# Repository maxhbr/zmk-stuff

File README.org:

#+title: Readme

* Building a Redox Style Split with xiaos + Shift Registers

similar to https://github.com/maxhbr/redox-meets-dao-choc-ble, but with a different set of electronics.

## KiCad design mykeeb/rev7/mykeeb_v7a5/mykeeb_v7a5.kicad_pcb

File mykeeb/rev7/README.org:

#+title: Readme

* Building a Redox Style Split with xiaos + Shift Registers

similar to https://github.com/maxhbr/redox-meets-dao-choc-ble, but with a different set of electronics.

*The shift registers are dropped for now, to iterate faster*

** The Idea:
*** Take the electronics from revxlp / uninarf
- Maybe with potential for (partial) JLC PCBA assembly
- using the xiao footprint from the TOTEM
*** Take the Rough layout from Redox
*** Adopt to the pinky stagger from the Kyria

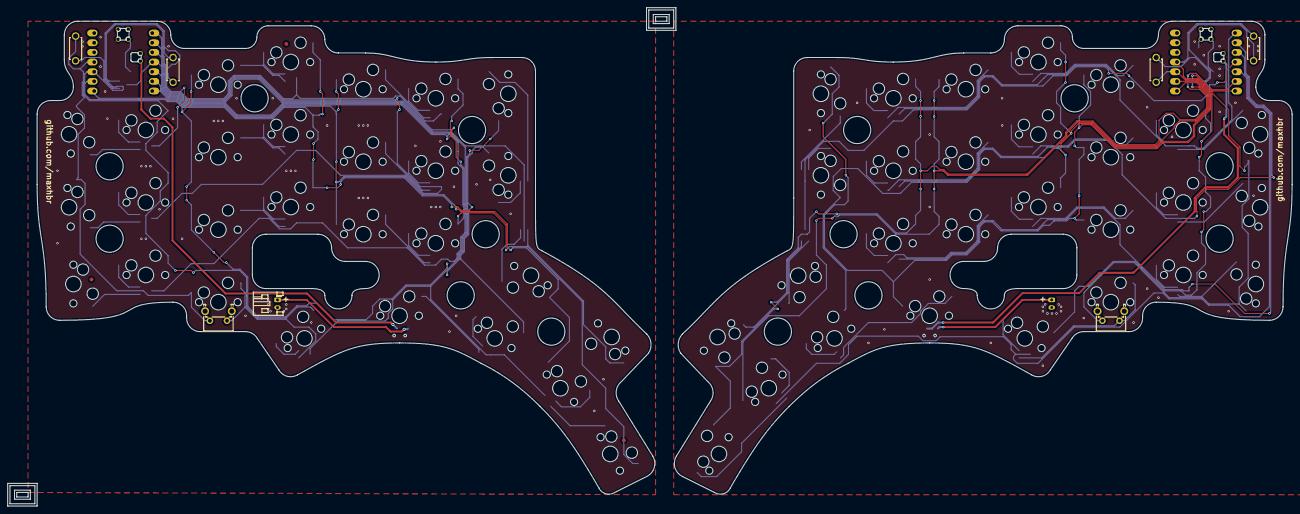
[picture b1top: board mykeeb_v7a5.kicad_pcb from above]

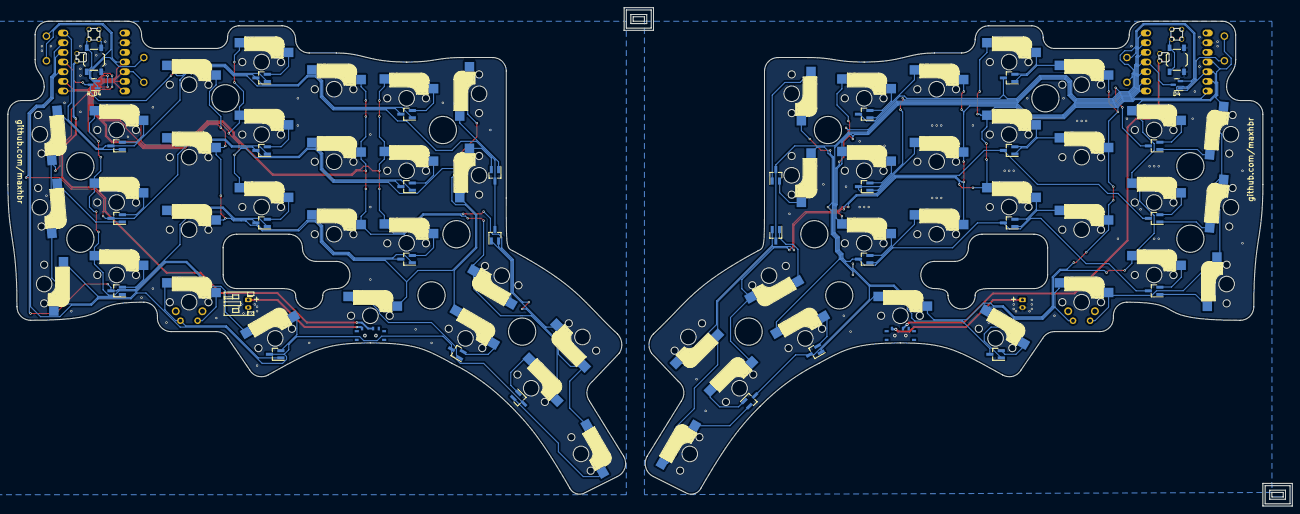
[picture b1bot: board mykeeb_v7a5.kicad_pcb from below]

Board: 2 copper layers, 337.5 x 131.0 mm, 103 parts (37 on the bottom side), 90 nets.

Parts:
BT1: Battery_Cell; JST_PH_S2B-PH-K_1x02_P2.00mm_Horizontal
D1, D2, D3, D4, D5, D6, D7, D8, D9, D10, D11, D12, D13, D14, D15: BAV70; SOT-23
FID1, FID2, FID3: Fiducial; Fiducial_1mm_Mask2mm
R_BT1: Battery_Cell; JST_PH_S2B-PH-K_1x02_P2.00mm_Horizontal
R_D1, R_D2, R_D3, R_D4, R_D5, R_D6, R_D7, R_D8, R_D9, R_D10, R_D11, R_D12, R_D13, R_D14, R_D15: BAV70; SOT-23
R_SA0, R_SA1, R_SA2, R_SA3, R_SA4, R_SA5: SW; CherryMX_Hotswap
R_SB0, R_SB1, R_SB2, R_SB3, R_SB4, R_SB5: SW; CherryMX_Hotswap
R_SC0, R_SC1, R_SC2, R_SC3, R_SC4, R_SC5: SW; CherryMX_Hotswap
R_SD0, R_SD1: SW_Push; PushSW
R_SD2: SW; CherryMX_Hotswap
R_SD3, R_SD4, R_SD5: SW; CherryMX_1.25U_Hotswap
R_SE0, R_SE3, R_SE4: SW; CherryMX_Hotswap
R_SE0_alt1: SW_Push; SW_Tactile_SPST_Angled_PTS645Vx39-2LFS
R_SE2: SW; CherryMX_1.25U_Hotswap
R_SW1: SW_Push; SW_SPST_TL3342
R_SW_bat1: SW_SPDT; switch-MSK-12C02-smd
R_U1: xiao-ble; xiao-ble-smd-cutout
SA0, SA1, SA2, SA3, SA4, SA5: SW; CherryMX_Hotswap
SB0, SB1, SB2, SB3, SB4, SB5: SW; CherryMX_Hotswap
SC0, SC1, SC2, SC3, SC4, SC5: SW; CherryMX_Hotswap
SD0, SD1: SW_Push; PushSW
SD2: SW; CherryMX_Hotswap
SD3, SD4, SD5: SW; CherryMX_1.25U_Hotswap
SE0, SE3, SE4: SW; CherryMX_Hotswap
SE0_alt1: SW_Push; SW_Tactile_SPST_Angled_PTS645Vx39-2LFS
SE2: SW; CherryMX_1.25U_Hotswap
SW1: SW_Push; SW_SPST_TL3342
SW_bat1: SW_SPDT; switch-MSK-12C02-smd
U1: xiao-ble; xiao-ble-smd-cutout
locked: SW; CherryMX_Hotswap
locked#2, locked#3, locked#4: SW; CherryMX_Hotswap

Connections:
BAT+: SW_bat1.2 (B), U1.19 (BAT)
GND: BT1.2 (-), SW1.2, U1.13 (GND), U1.18 (GND), U1.20 (GND)
unnamed: D1.1 (A1), SA0.2
unnamed: D1.2 (A2), SA1.1
unnamed: D2.1 (A1), SB0.2
unnamed: D2.2 (A2), SB1.1
unnamed: D3.1 (A1), SC0.2
unnamed: D3.2 (A2), SC1.1
unnamed: D4.1 (A1), SD0.2
unnamed: D4.2 (A2), SD1.1
unnamed: D5.1 (A1), SE0.2, SE0_alt1.1
unnamed: D5.2 (A2), locked#4.1
unnamed: D6.1 (A1), SA2.2
unnamed: D6.2 (A2), SA3.1
unnamed: D7.1 (A1), SB2.2
unnamed: D7.2 (A2), SB3.1
unnamed: D8.1 (A1), SC2.2
unnamed: D8.2 (A2), SC3.1
unnamed: D9.1 (A1), SD2.2
unnamed: D9.2 (A2), SD3.1
unnamed: D10.1 (A1), SE2.2
unnamed: D10.2 (A2), SE3.1
unnamed: D11.1 (A1), SA4.2
unnamed: D11.2 (A2), SA5.1
unnamed: D12.1 (A1), SB4.2
unnamed: D12.2 (A2), SB5.1
unnamed: D13.1 (A1), SC4.2
unnamed: D13.2 (A2), SC5.1
unnamed: D14.1 (A1), SD4.2
unnamed: D14.2 (A2), SD5.1
unnamed: D15.1 (A1), SE4.2
unnamed: D15.2 (A2), locked.1
unnamed: R_D1.1 (A1), R_SA0.2
unnamed: R_D1.2 (A2), R_SA1.1
unnamed: R_D2.1 (A1), R_SB0.2
unnamed: R_D2.2 (A2), R_SB1.1
unnamed: R_D3.1 (A1), R_SC0.2
unnamed: R_D3.2 (A2), R_SC1.1
unnamed: R_D4.1 (A1), R_SD0.2
unnamed: R_D4.2 (A2), R_SD1.1
unnamed: R_D5.1 (A1), R_SE0.2, R_SE0_alt1.1
unnamed: R_D5.2 (A2), locked#2.1
unnamed: R_D6.1 (A1), R_SA2.2
unnamed: R_D6.2 (A2), R_SA3.1
unnamed: R_D7.1 (A1), R_SB2.2
unnamed: R_D7.2 (A2), R_SB3.1
unnamed: R_D8.1 (A1), R_SC2.2
unnamed: R_D8.2 (A2), R_SC3.1
unnamed: R_D9.1 (A1), R_SD2.2
unnamed: R_D9.2 (A2), R_SD3.1
unnamed: R_D10.1 (A1), R_SE2.2
unnamed: R_D10.2 (A2), R_SE3.1
unnamed: R_D11.1 (A1), R_SA4.2
unnamed: R_D11.2 (A2), R_SA5.1
unnamed: R_D12.1 (A1), R_SB4.2
unnamed: R_D12.2 (A2), R_SB5.1
unnamed: R_D13.1 (A1), R_SC4.2
unnamed: R_D13.2 (A2), R_SC5.1
unnamed: R_D14.1 (A1), R_SD4.2
unnamed: R_D14.2 (A2), R_SD5.1
unnamed: R_D15.1 (A1), R_SE4.2
unnamed: R_D15.2 (A2), locked#3.1
RESET: SW1.1, U1.17 (RESET)
R_BAT+: R_SW_bat1.2 (B), R_U1.19 (BAT)
R_GND: R_SW1.2, R_U1.13 (GND), R_U1.18 (GND), R_U1.20 (GND)
R_RESET: R_SW1.1, R_U1.17 (RESET)
R_VBAT: R_BT1.1 (+), R_SW_bat1.1 (A)
R_col0: R_SA0.1, R_SB0.1, R_SC0.1, R_SD0.1, R_SE0.1, R_SE0_alt1.2, R_U1.11 (A6_MOSI/1.15)
R_col1: R_SA1.2, R_SB1.2, R_SC1.2, R_SD1.2, R_U1.10 (A5_MISO/1.14), locked#2.2
R_col2: R_SA2.1, R_SB2.1, R_SC2.1, R_SD2.1, R_SE2.1, R_U1.9 (A7_SCK/1.13)
R_col3: R_SA3.2, R_SB3.2, R_SC3.2, R_SD3.2, R_SE3.2, R_U1.8 (B9_RX/1.12)
R_col4: R_SA4.1, R_SB4.1, R_SC4.1, R_SD4.1, R_SE4.1, R_U1.7 (B8_TX/1.11)
R_col5: R_SA5.2, R_SB5.2, R_SC5.2, R_SD5.2, R_U1.6 (A9_SCL/0.05_H), locked#3.2
R_rowA: R_D1.3 (K), R_D6.3 (K), R_D11.3 (K), R_U1.1 (A2/0.02_H)
R_rowB: R_D2.3 (K), R_D7.3 (K), R_D12.3 (K), R_U1.2 (A4/0.03_H)
R_rowC: R_D3.3 (K), R_D8.3 (K), R_D13.3 (K), R_U1.3 (A10/0.28)
R_rowD: R_D4.3 (K), R_D9.3 (K), R_D14.3 (K), R_U1.4 (A11/0.29)
R_rowE: R_D5.3 (K), R_D10.3 (K), R_D15.3 (K), R_U1.5 (A8_SDA/0.04_H)
VBAT: BT1.1 (+), SW_bat1.1 (A)
col0: SA0.1, SB0.1, SC0.1, SD0.1, SE0.1, SE0_alt1.2, U1.11 (A6_MOSI/1.15)
col1: SA1.2, SB1.2, SC1.2, SD1.2, U1.10 (A5_MISO/1.14), locked#4.2
col2: SA2.1, SB2.1, SC2.1, SD2.1, SE2.1, U1.9 (A7_SCK/1.13)
col3: SA3.2, SB3.2, SC3.2, SD3.2, SE3.2, U1.8 (B9_RX/1.12)
col4: SA4.1, SB4.1, SC4.1, SD4.1, SE4.1, U1.7 (B8_TX/1.11)
col5: SA5.2, SB5.2, SC5.2, SD5.2, U1.6 (A9_SCL/0.05_H), locked.2
rowA: D1.3 (K), D6.3 (K), D11.3 (K), U1.1 (A2/0.02_H)
rowB: D2.3 (K), D7.3 (K), D12.3 (K), U1.2 (A4/0.03_H)
rowC: D3.3 (K), D8.3 (K), D13.3 (K), U1.3 (A10/0.28)
rowD: D4.3 (K), D9.3 (K), D14.3 (K), U1.4 (A11/0.29)
rowE: D5.3 (K), D10.3 (K), D15.3 (K), U1.5 (A8_SDA/0.04_H)

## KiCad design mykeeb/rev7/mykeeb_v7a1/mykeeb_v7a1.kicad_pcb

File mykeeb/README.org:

* mykeeb
** Why not an existing keeb
- [[https://github.com/mattdibi/redox-keyboard][REDOX]]
  - is very close
    - no HotSwap in the open source variant
- [[https://github.com/tadfisher/nyx-kb/][NYX]]
  - not happy with the thumb cluster
- Kyria
  - not OSS
  - to less keys
- [[https://github.com/omkbd/ErgoDash][ErgoDash]]
  - similar to REDOX
  - thumb cluster is forced to use one 2U
- [[https://github.com/jpconstantineau/ErgoTravel][ErgoTravel]]
- Zordiak is not OSS
- [[https://github.com/Pekaso/fortitude60][fortitude60]]
  - MCU is *Beetle USB 32u4* -> not supported by ZMK
- [[https://github.com/KarlK90/yaemk-split-kb][YAEMK]]
  - not supported by ZMK
- [[https://github.com/vlkv/avalanche][The Avalanche keyboard]]
  - tbd.

Other interesting Keyboards are Lily58, Lotus58, Sofle,

** Goals
- it *must* be fully OSS
  - especially also PCB and case
- it *must* support ZMK
  - it *could* have QMK support
- it *must* support 3D printed case and switch plate
  - it *should* have tenting support
- it *should* be split
- it *must* have columnar staggered layout
  - similar to Kyria or REDOX
    - Kyria aggressiveness is great!
- it *should* have _a lot_ of keys:
  - got used to 35 keys per side. Maybe 30 could also be sufficient.
  - it *must* have a thumb cluster
    - maybe a combination of REDOX-style and NYX-style
  - it *must* have 6 cols
    - it *should* have 7 cols, i.e. an additional center column
  - it *should* have a Number row
  - it *could* have arrow keys
  - it *does not need* to have encoder support
- it *could* have 1.5u keys for parts of the thumb cluster
- it *should* have MX style switches
  - it *could* also have Choc compatibility
    - maybe specifically for the thumb cluster?
- it *should* have HotSwap
  - preferred via Kailh sockets
- MCU *should* be mounted visible, and not on the back side
  - MCU *could* have two sockets to choose orientation per side
    - I like them chip side up
  - maybe similar to NYX, Kyria or crkbd
  - MCU *should* use a standard interconnect like Pro Micro
- it *should* have PCB support for a switch and battery connections
- it *could* expose i2c for trackball support
- it *could* have RGB-LED for feedback regarding activated layers or modifier
  - could also be done via display
  - could also be done via the trackpoint led
  - it *does not need* any further LED stuff

** How to start?
- base on something
  - REDOX
    - no HotSwap
  - ErgoDash
    - one less thumb key
  - NYX
    - has MX+Chock footprints, but does not fir 5pin MX
    - uses Horizon EDA
- from scratch
  - https://github.com/ruiqimao/keyboard-pcb-guide
  - which MCU
    - nRF52840
      - Nice!Nano
        - can easily do >=42 switches per side (41 on reviung41), using 6+7 GPIO pins
      - nRF52830 Dongle
        - 15 GPIOs
        - no LiPo support
      - Seeed XIAO BLE
        - has 11 GPIO pins
          - max 30=5*6 switches?
          - hummingbird has 30 switches
    - esp32

* Links:
- https://github.com/diimdeep/awesome-split-keyboards

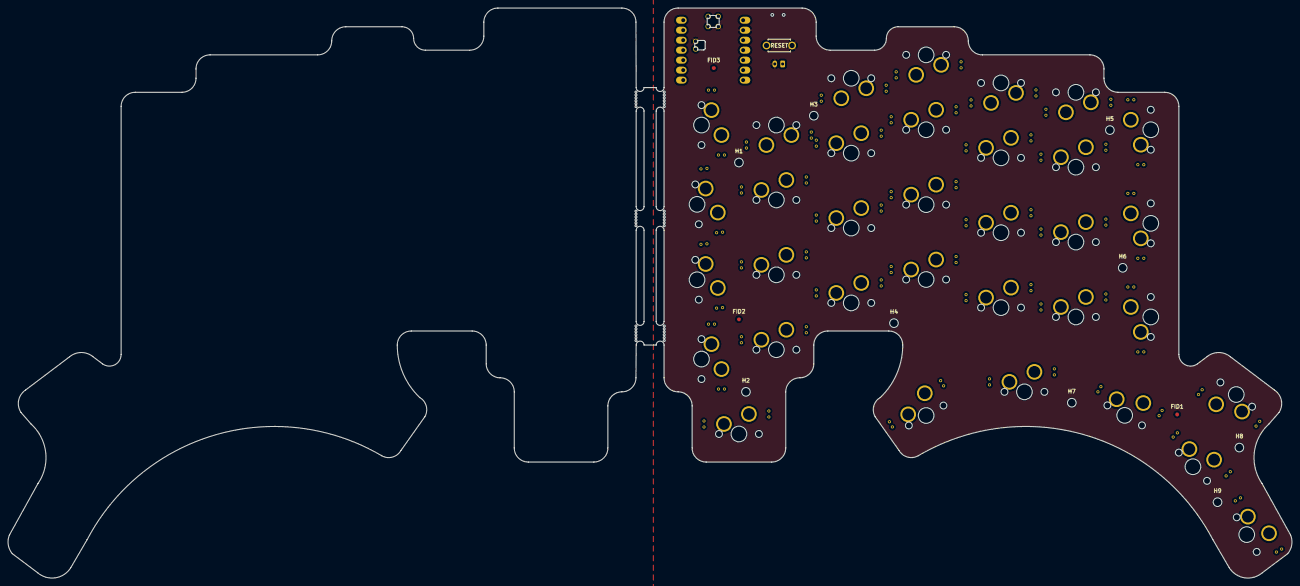
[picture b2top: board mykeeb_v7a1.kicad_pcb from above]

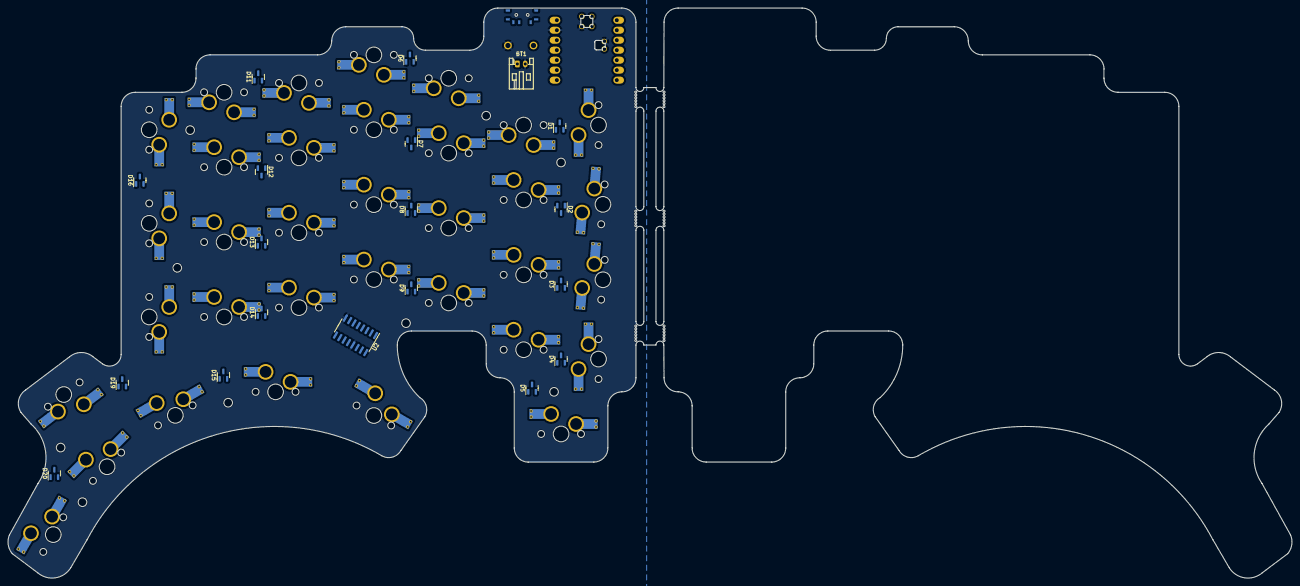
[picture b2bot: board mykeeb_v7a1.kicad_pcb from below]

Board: 2 copper layers, 326.6 x 145.0 mm, 68 parts (20 on the bottom side), 55 nets, no tracks yet.

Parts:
BT1: Battery_Cell; JST_PH_S2B-PH-K_1x02_P2.00mm_Horizontal
D1, D2, D3, D4, D5, D6, D7, D8, D9, D11, D12, D13, D14, D15, D16, D19, D20: BAV70; SOT-23
FID1, FID2, FID3: Fiducial; Fiducial_1mm_Mask2mm
H1, H2, H3, H4, H5, H6, H7, H8, H9: MountingHole; MountingHole_2.2mm_M2_DIN965
S0, S1, S2, S3, S4, S5, S6, S7, S10, S11, S12, S13, S14, S15, S20, S21, S22, S23, S24, S25, S30, S31, S32, S33, S34, S35, S36, S37, S40, S41, S42, S43, S44, S45: SW; MX-1U-Hotswap
SW_bat1: SW_SPDT; switch-MSK-12C02-smd
SW_reset1: SW_Push; ResetSW
U1: xiao-ble; xiao-ble-smd-cutout
U2: 74HC595; SOP-16_3.9x9.9mm_P1.27mm

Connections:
BAT+: SW_bat1.2 (B), U1.19 (BAT)
GND: BT1.2 (-), SW_reset1.2, U1.13 (GND), U1.18 (GND), U1.20 (GND), U2.8 (GND), U2.13 (~OE)
IO_CS: U1.8 (B9_RX/1.12), U2.12 (RCLK)
MOSI: U1.11 (A6_MOSI/1.15), U2.14 (SER)
unnamed: D1.1 (A1), S0.2
unnamed: D1.2 (A2), S1.1
unnamed: D2.1 (A1), S10.2
unnamed: D2.2 (A2), S11.1
unnamed: D3.1 (A1), S20.2
unnamed: D3.2 (A2), S21.1
unnamed: D4.1 (A1), S30.2
unnamed: D4.2 (A2), S31.1
unnamed: D5.1 (A1), S40.2
unnamed: D5.2 (A2), S41.1
unnamed: D6.1 (A1), S2.2
unnamed: D6.2 (A2), S3.1
unnamed: D7.1 (A1), S12.2
unnamed: D7.2 (A2), S13.1
unnamed: D8.1 (A1), S22.2
unnamed: D8.2 (A2), S23.1
unnamed: D9.1 (A1), S32.2
unnamed: D9.2 (A2), S33.1
unnamed: D11.1 (A1), S4.2
unnamed: D11.2 (A2), S5.1
unnamed: D12.1 (A1), S14.2
unnamed: D12.2 (A2), S15.1
unnamed: D13.1 (A1), S24.2
unnamed: D13.2 (A2), S25.1
unnamed: D14.1 (A1), S34.2
unnamed: D14.2 (A2), S35.1
unnamed: D15.1 (A1), S42.2
unnamed: D15.2 (A2), S43.1
unnamed: D16.1 (A1), S6.2
unnamed: D16.2 (A2), S7.1
unnamed: D19.1 (A1), S36.2
unnamed: D19.2 (A2), S37.1
unnamed: D20.1 (A1), S44.2
unnamed: D20.2 (A2), S45.1
RESET: SW_reset1.1, U1.17 (RESET)
SCK: U1.9 (A7_SCK/1.13), U2.11 (SRCLK)
VBAT: BT1.1 (+), SW_bat1.3 (C)
VCC: U1.12 (3V3), U2.10 (~SRCLR), U2.16 (VCC)
col0: S0.1, S10.1, S20.1, S30.1, S40.1
col1: S1.2, S11.2, S21.2, S31.2, S41.2
col2: S2.1, S12.1, S22.1, S32.1, S42.1
col3: S3.2, S13.2, S23.2, S33.2, S43.2
col4: S4.1, S14.1, S24.1, S34.1, S44.1
col5: S5.2, S15.2, S25.2, S35.2, S45.2
col6: S6.1, S36.1
col7: S7.2, S37.2
row0: D1.3 (K), D6.3 (K), D11.3 (K), D16.3 (K)
row1: D2.3 (K), D7.3 (K), D12.3 (K)
row2: D3.3 (K), D8.3 (K), D13.3 (K)
row3: D4.3 (K), D9.3 (K), D14.3 (K), D19.3 (K)
row4: D5.3 (K), D15.3 (K), D20.3 (K)

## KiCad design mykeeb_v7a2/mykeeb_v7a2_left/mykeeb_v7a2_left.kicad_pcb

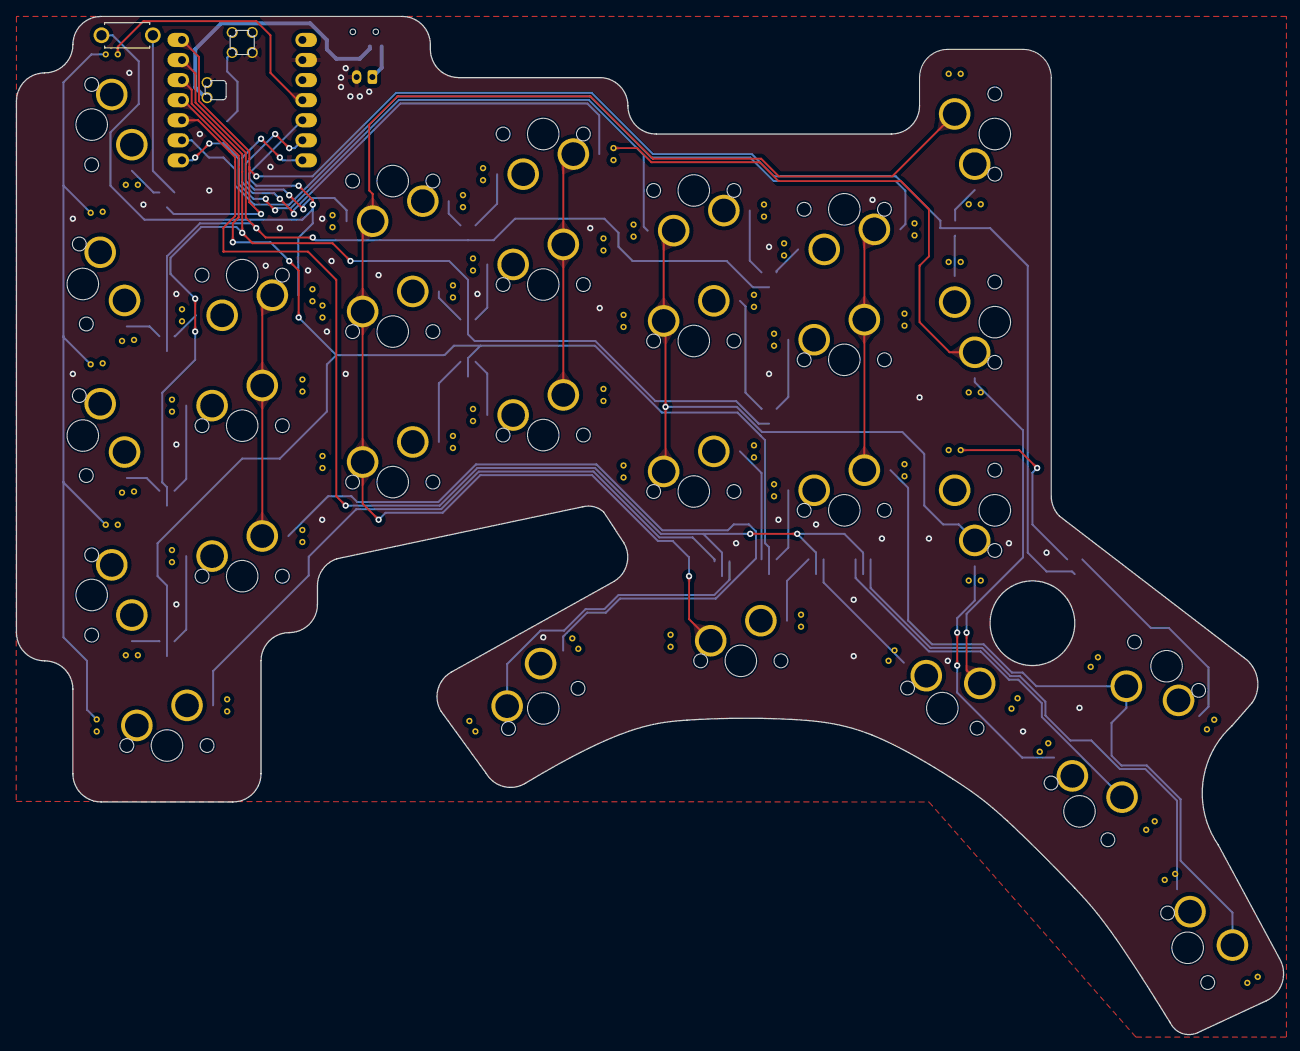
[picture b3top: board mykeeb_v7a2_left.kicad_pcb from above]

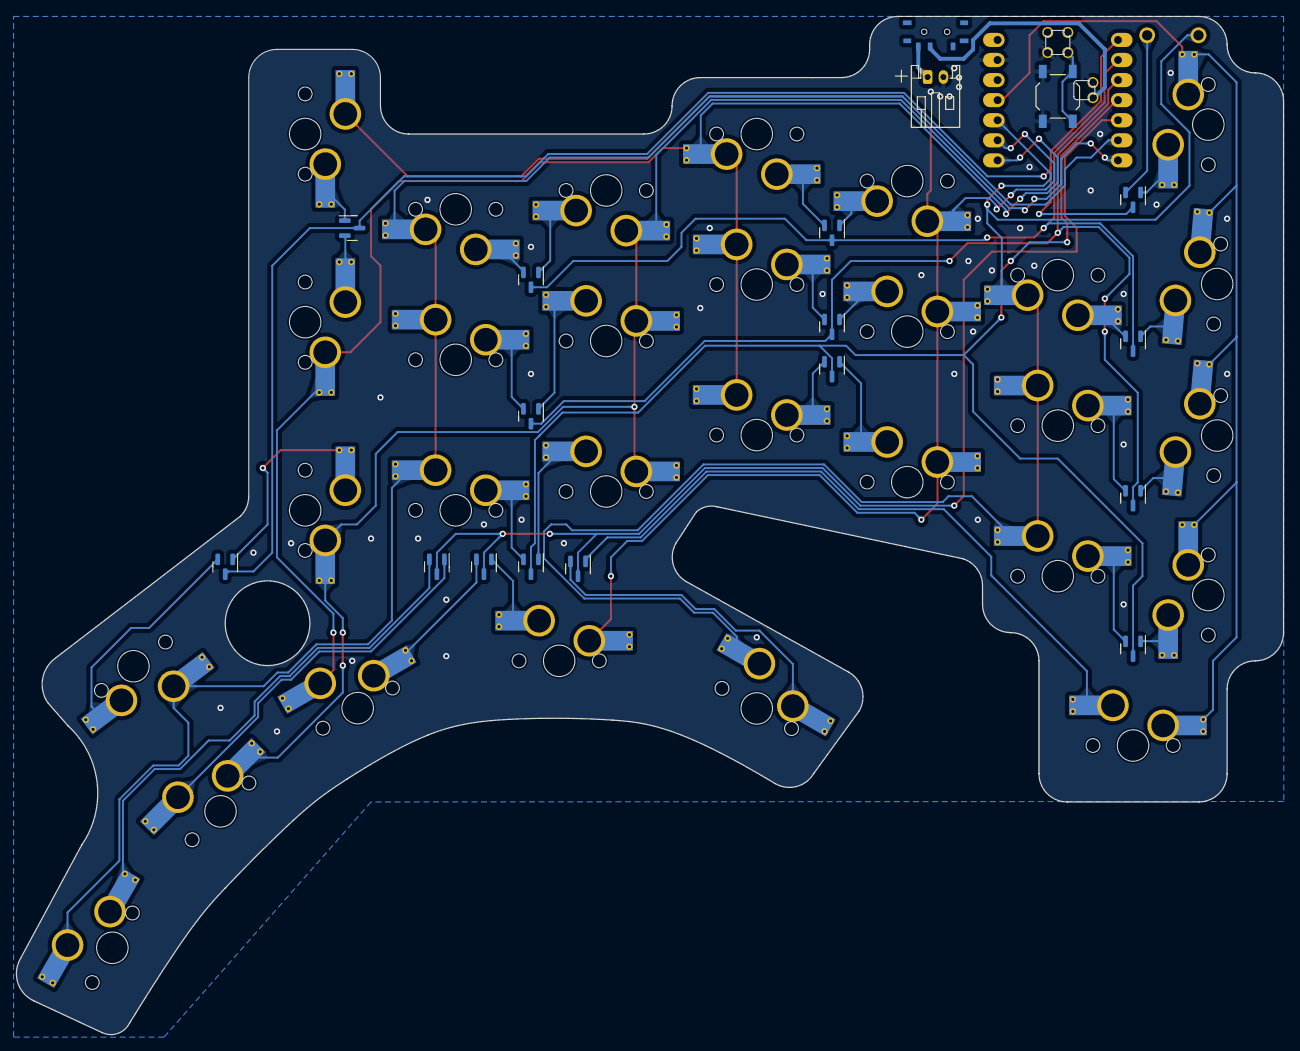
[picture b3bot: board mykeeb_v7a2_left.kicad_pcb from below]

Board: 2 copper layers, 160.4 x 128.9 mm, 49 parts (18 on the bottom side), 45 nets.

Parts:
L_BT1: Battery_Cell; JST_PH_S2B-PH-K_1x02_P2.00mm_Horizontal
L_D1, L_D2, L_D3, L_D4, L_D5, L_D6, L_D7, L_D8, L_D9, L_D10, L_D11, L_D12, L_D13, L_D14, L_D15: BAV70; SOT-23
L_S0, L_S2, L_S3, L_S4, L_S5, L_S10, L_S11, L_S12, L_S13, L_S14, L_S15, L_S20, L_S21, L_S22, L_S23, L_S24, L_S25, L_S30, L_S31, L_S32, L_S33, L_S34, L_S35, L_S40, L_S42, L_S43, L_S44: SW; MX-1U-Hotswap
L_S1: SW_Push; PushSW
L_SW_bat1: SW_SPDT; switch-MSK-12C02-smd
L_SW_reset1: SW_Push; SW_SPST_TL3342
L_U1: xiao-ble; xiao-ble-smd-cutout
locked: SW; MX-1U-Hotswap
locked#2: SW; MX-1U-Hotswap

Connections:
GND: L_BT1.2 (-), L_SW_reset1.2, L_U1.13 (GND), L_U1.18 (GND), L_U1.20 (GND)
L_BAT+: L_SW_bat1.2 (B), L_U1.19 (BAT)
L_COL0: L_S0.1, L_S10.1, L_S20.1, L_S30.1, L_S40.1, L_U1.11 (A6_MOSI/1.15)
L_COL1: L_S1.2, L_S11.1, L_S21.2, L_S31.2, L_U1.10 (A5_MISO/1.14), locked.2
L_COL2: L_S2.2, L_S12.2, L_S22.1, L_S32.1, L_S42.1, L_U1.9 (A7_SCK/1.13)
L_COL3: L_S3.1, L_S13.1, L_S23.2, L_S33.2, L_S43.2, L_U1.8 (B9_RX/1.12)
L_COL4: L_S4.1, L_S14.2, L_S24.1, L_S34.1, L_S44.1, L_U1.7 (B8_TX/1.11)
L_COL5: L_S5.2, L_S15.1, L_S25.2, L_S35.2, L_U1.6 (A9_SCL/0.05_H), locked#2.2
L_RESET: L_SW_reset1.1, L_U1.17 (RESET)
L_ROW0: L_D1.3 (K), L_D6.3 (K), L_D11.3 (K), L_U1.1 (A2/0.02_H)
L_ROW1: L_D2.3 (K), L_D7.3 (K), L_D12.3 (K), L_U1.2 (A4/0.03_H)
L_ROW2: L_D3.3 (K), L_D8.3 (K), L_D13.3 (K), L_U1.3 (A10/0.28)
L_ROW3: L_D4.3 (K), L_D9.3 (K), L_D14.3 (K), L_U1.4 (A11/0.29)
L_ROW4: L_D5.3 (K), L_D10.3 (K), L_D15.3 (K), L_U1.5 (A8_SDA/0.04_H)
L_VBAT: L_BT1.1 (+), L_SW_bat1.3 (C)
unnamed: L_D1.1 (A1), L_S0.2
unnamed: L_D1.2 (A2), L_S1.1
unnamed: L_D2.1 (A1), L_S10.2
unnamed: L_D2.2 (A2), L_S11.2
unnamed: L_D3.1 (A1), L_S20.2
unnamed: L_D3.2 (A2), L_S21.1
unnamed: L_D4.1 (A1), L_S30.2
unnamed: L_D4.2 (A2), L_S31.1
unnamed: L_D5.1 (A1), L_S40.2
unnamed: L_D5.2 (A2), locked.1
unnamed: L_D6.1 (A1), L_S2.1
unnamed: L_D6.2 (A2), L_S3.2
unnamed: L_D7.1 (A1), L_S12.1
unnamed: L_D7.2 (A2), L_S13.2
unnamed: L_D8.1 (A1), L_S22.2
unnamed: L_D8.2 (A2), L_S23.1
unnamed: L_D9.1 (A1), L_S32.2
unnamed: L_D9.2 (A2), L_S33.1
unnamed: L_D10.1 (A1), L_S42.2
unnamed: L_D10.2 (A2), L_S43.1
unnamed: L_D11.1 (A1), L_S4.2
unnamed: L_D11.2 (A2), L_S5.1
unnamed: L_D12.1 (A1), L_S14.1
unnamed: L_D12.2 (A2), L_S15.2
unnamed: L_D13.1 (A1), L_S24.2
unnamed: L_D13.2 (A2), L_S25.1
unnamed: L_D14.1 (A1), L_S34.2
unnamed: L_D14.2 (A2), L_S35.1
unnamed: L_D15.1 (A1), L_S44.2
unnamed: L_D15.2 (A2), locked#2.1

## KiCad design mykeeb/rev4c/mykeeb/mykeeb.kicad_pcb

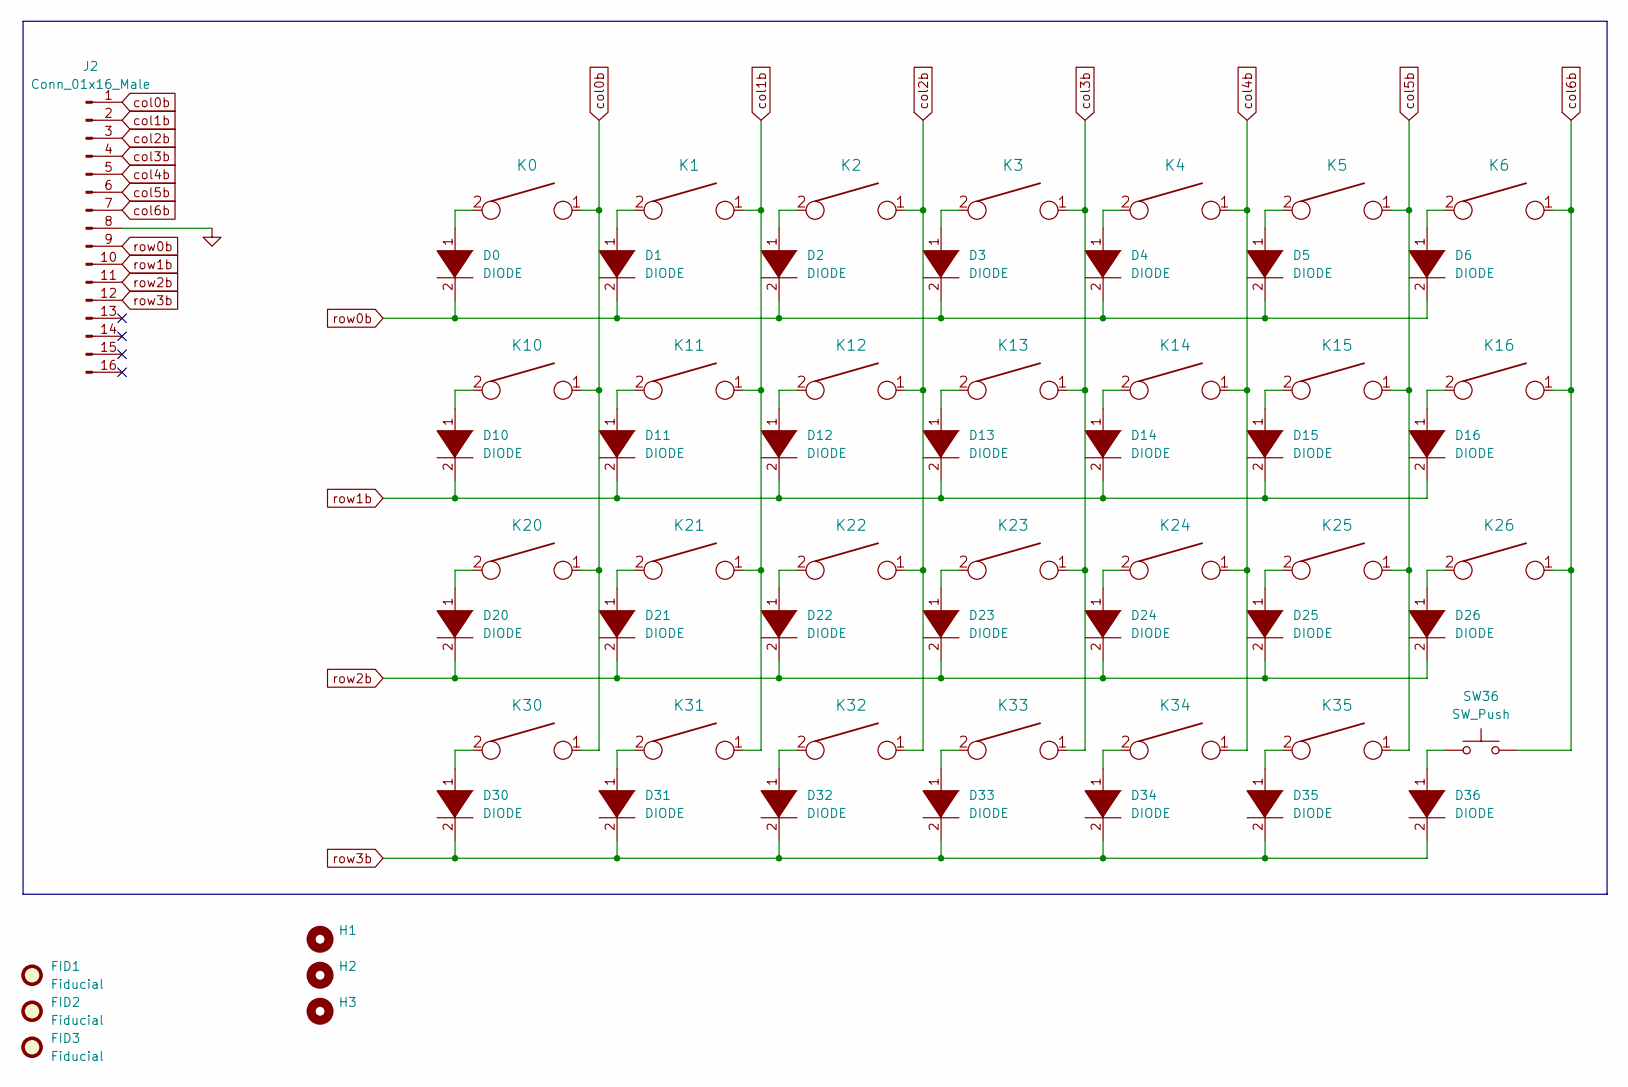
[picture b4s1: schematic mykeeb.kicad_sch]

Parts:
D0, D1, D2, D3, D4, D5, D6, D10, D11, D12, D13, D14, D15, D16, D20, D21, D22, D23, D24, D25, D26, D30, D31, D32, D33, D34, D35: DIODE; my_dual_D_SOD123F_v2
D36: DIODE; my_dual_D_SOD123F_v2b
FID1, FID2, FID3: Fiducial; Fiducial_1mm_Mask2mm
H1, H2, H3: (no value)
J2: Conn_01x16_Male; adapterBoard
K0, K1, K2, K3, K4, K5, K6, K10, K11, K12, K13, K14, K15, K20, K21, K22, K23, K24, K25, K26, K30, K31, K32, K33, K34, K35: KEYSW; Kailh_socket_MX_reversible_1u
K16: KEYSW; Kailh_socket_MX_reversible_1.5u
SW36: SW_Push; SW_PUSH_6mm_H7.3mm

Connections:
GND: J2.8
unnamed: D0.1 (K), K0.2
unnamed: D1.1 (K), K1.2
unnamed: D2.1 (K), K2.2
unnamed: D3.1 (K), K3.2
unnamed: D4.1 (K), K4.2
unnamed: D5.1 (K), K5.2
unnamed: D6.1 (K), K6.2
unnamed: D10.1 (K), K10.2
unnamed: D11.1 (K), K11.2
unnamed: D12.1 (K), K12.2
unnamed: D13.1 (K), K13.2
unnamed: D14.1 (K), K14.2
unnamed: D15.1 (K), K15.2
unnamed: D16.1 (K), K16.2
unnamed: D20.1 (K), K20.2
unnamed: D21.1 (K), K21.2
unnamed: D22.1 (K), K22.2
unnamed: D23.1 (K), K23.2
unnamed: D24.1 (K), K24.2
unnamed: D25.1 (K), K25.2
unnamed: D26.1 (K), K26.2
unnamed: D30.1 (K), K30.2
unnamed: D31.1 (K), K31.2
unnamed: D32.1 (K), K32.2
unnamed: D33.1 (K), K33.2
unnamed: D34.1 (K), K34.2
unnamed: D35.1 (K), K35.2
unnamed: D36.1 (K), SW36.1
col0b: J2.1, K0.1, K10.1, K20.1, K30.1
col1b: J2.2, K1.1, K11.1, K21.1, K31.1
col2b: J2.3, K2.1, K12.1, K22.1, K32.1
col3b: J2.4, K3.1, K13.1, K23.1, K33.1
col4b: J2.5, K4.1, K14.1, K24.1, K34.1
col5b: J2.6, K5.1, K15.1, K25.1, K35.1
col6b: J2.7, K6.1, K16.1, K26.1, SW36.2
row0b: D0.2 (A), D1.2 (A), D2.2 (A), D3.2 (A), D4.2 (A), D5.2 (A), D6.2 (A), J2.9
row1b: D10.2 (A), D11.2 (A), D12.2 (A), D13.2 (A), D14.2 (A), D15.2 (A), D16.2 (A), J2.10
row2b: D20.2 (A), D21.2 (A), D22.2 (A), D23.2 (A), D24.2 (A), D25.2 (A), D26.2 (A), J2.11
row3b: D30.2 (A), D31.2 (A), D32.2 (A), D33.2 (A), D34.2 (A), D35.2 (A), D36.2 (A), J2.12

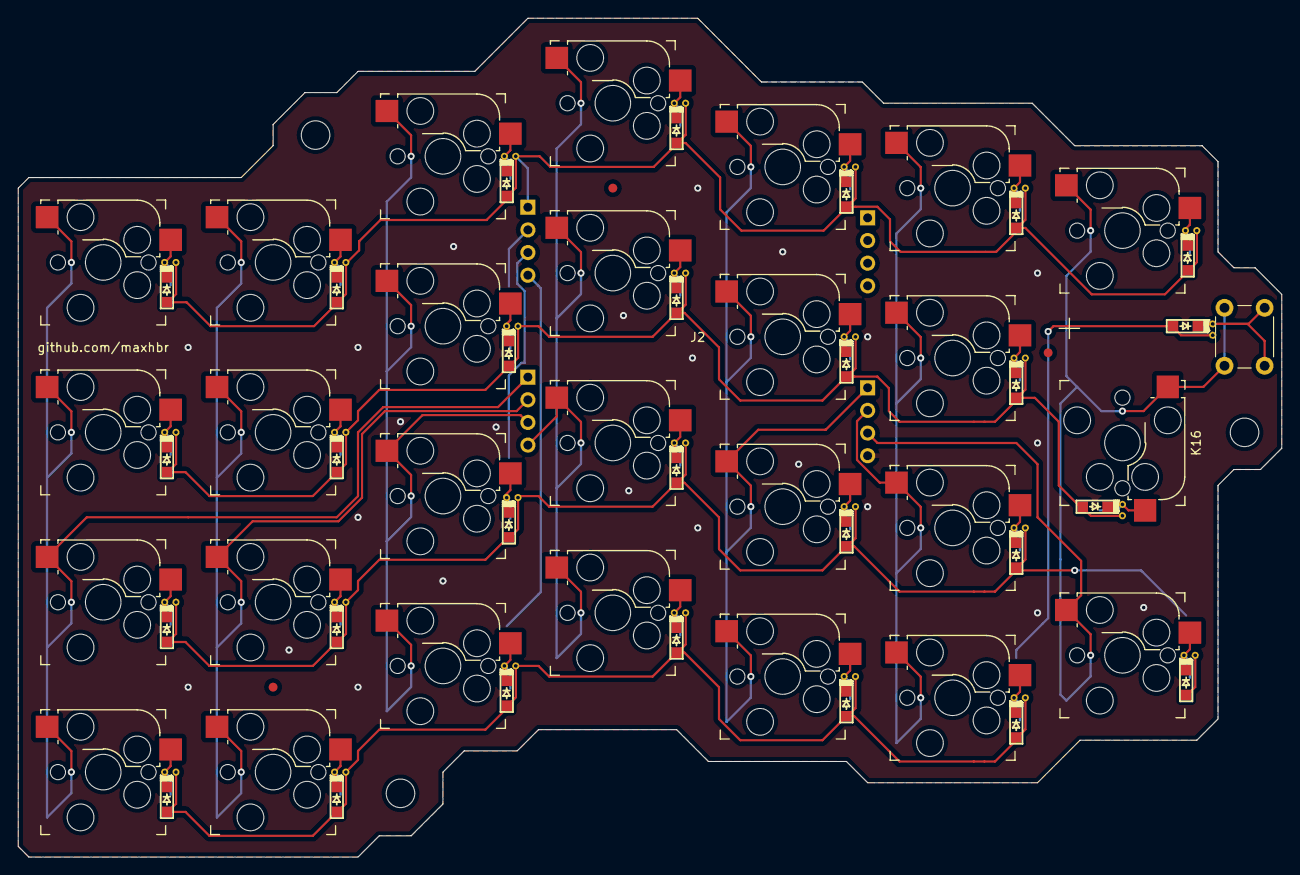
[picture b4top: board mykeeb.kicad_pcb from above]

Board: 2 copper layers, 141.7 x 94.1 mm, 63 parts (0 on the bottom side), 39 nets.

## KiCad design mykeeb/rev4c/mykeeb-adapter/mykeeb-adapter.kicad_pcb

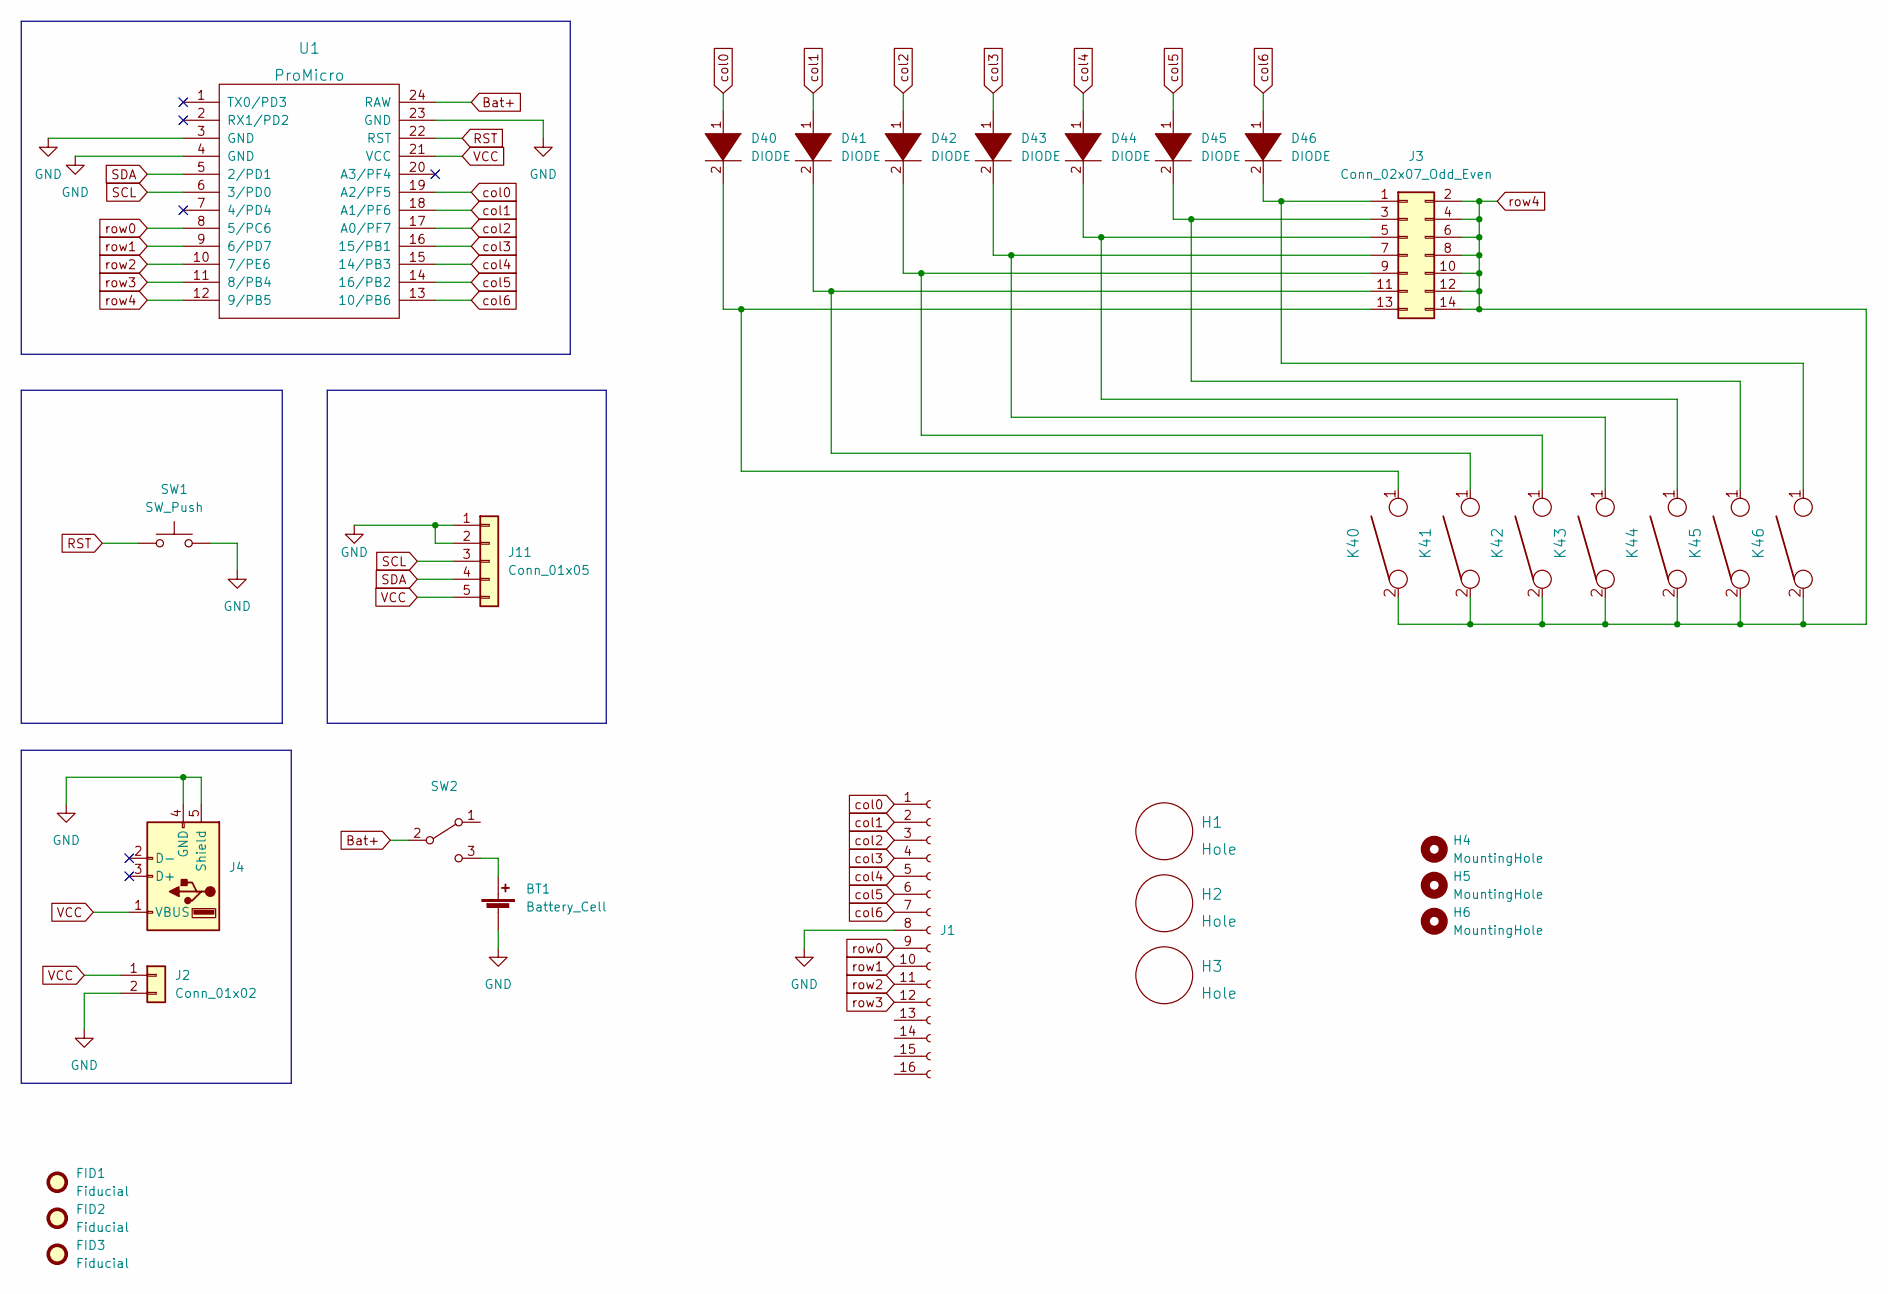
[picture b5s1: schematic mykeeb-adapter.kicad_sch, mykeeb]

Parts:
BT1: Battery_Cell; JST_PH_S2B-PH-K_1x02_P2.00mm_Horizontal
D40, D41, D42, D43, D44, D45, D46: DIODE; my_dual_D_SOD123F_v2b
FID1, FID2, FID3: Fiducial; Fiducial_1mm_Mask2mm
H1, H2, H3: Hole; breakaway
H4, H5, H6: MountingHole; MountingHole_3.2mm_M3
J1, J4: (no value)
J2: Conn_01x02; PinHeader_1x02_P2.54mm_Vertical
J3: Conn_02x07_Odd_Even; PinHeader_2x07_P2.54mm_Vertical
J11: Conn_01x05; PinSocket_1x05_P2.54mm_Vertical
K40, K41, K43, K44, K45, K46: KEYSW; Kailh_socket_MX_reversible_1u
K42: KEYSW; Kailh_socket_MX_reversible_1.25u
SW1: SW_Push; SW_PUSH_6mm
SW2: (no value)
U1: ProMicro; my_reversible_Pro_Micro

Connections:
Bat+: SW2.2 (B), U1.24 (RAW)
GND: BT1.2 (-), J1.8, J2.2, J4.4 (GND), J4.5 (Shield), J11.1, J11.2, SW1.2, U1.3 (GND), U1.4 (GND), U1.23 (GND)
unnamed: BT1.1 (+), SW2.3 (C)
unnamed: D40.2 (A), J3.13, K40.1
unnamed: D41.2 (A), J3.11, K41.1
unnamed: D42.2 (A), J3.9, K42.1
unnamed: D43.2 (A), J3.7, K43.1
unnamed: D44.2 (A), J3.5, K44.1
unnamed: D45.2 (A), J3.3, K45.1
unnamed: D46.2 (A), J3.1, K46.1
RST: SW1.1, U1.22 (RST)
SCL: J11.3, U1.6 (3/PD0)
SDA: J11.4, U1.5 (2/PD1)
VCC: J2.1, J4.1 (VBUS), J11.5, U1.21 (VCC)
col0: D40.1 (K), J1.1, U1.19 (A2/PF5)
col1: D41.1 (K), J1.2, U1.18 (A1/PF6)
col2: D42.1 (K), J1.3, U1.17 (A0/PF7)
col3: D43.1 (K), J1.4, U1.16 (15/PB1)
col4: D44.1 (K), J1.5, U1.15 (14/PB3)
col5: D45.1 (K), J1.6, U1.14 (16/PB2)
col6: D46.1 (K), J1.7, U1.13 (10/PB6)
row0: J1.9, U1.8 (5/PC6)
row1: J1.10, U1.9 (6/PD7)
row2: J1.11, U1.10 (7/PE6)
row3: J1.12, U1.11 (8/PB4)
row4: J3.2, J3.4, J3.6, J3.8, J3.10, J3.12, J3.14, K40.2, K41.2, K42.2, K43.2, K44.2, K45.2, K46.2, U1.12 (9/PB5)
